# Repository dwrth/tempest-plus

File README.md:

# Tempest-Plus

A remix of the [Tempest](https://github.com/thrly/tempest) keyboard by Oliver Thurley.

Remixed by **dwrth (David Werth)** with:

* An additional number row
* The pinky stretch key moved up by one U

Ergogen configuration included.

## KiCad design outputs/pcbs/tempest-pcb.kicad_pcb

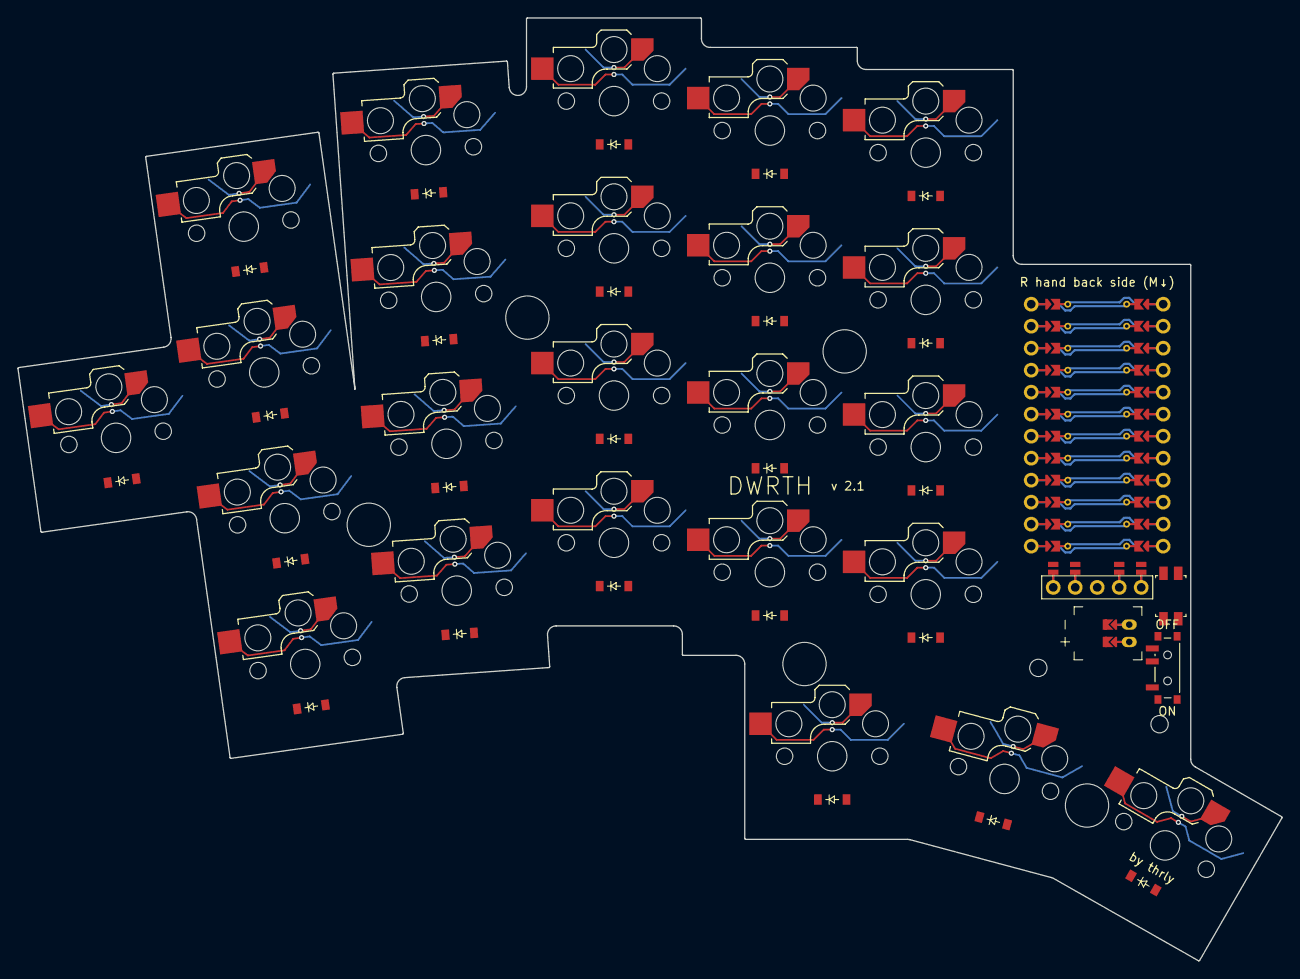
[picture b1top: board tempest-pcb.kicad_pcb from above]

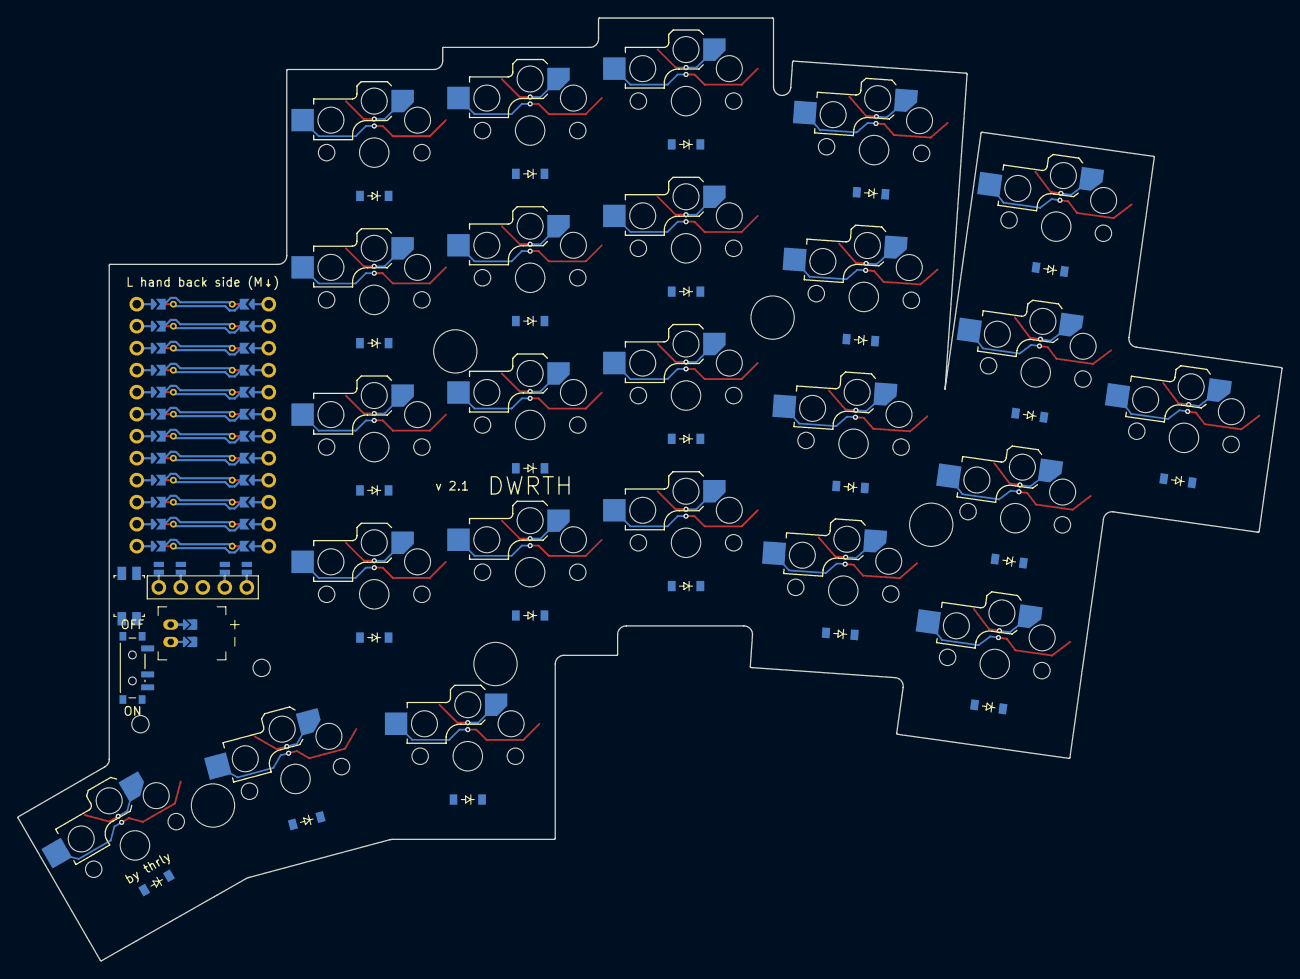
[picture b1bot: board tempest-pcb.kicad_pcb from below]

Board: 2 copper layers, 146.0 x 108.9 mm, 60 parts (24 on the bottom side), 49 nets.

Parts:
D1, D2, D3, D4, D5, D6, D7, D8, D9, D10, D11, D12, D13, D14, D15, D16, D17, D18, D19, D20, D21, D22, D23, D24: diode_tht_sod123
DISP1: display_nice_view
JST1: battery_connector_jst_ph_2
MCU1: mcu_nice_nano
MH1, MH2, MH3, MH4, MH5, MH6, MH7: mounting_hole_npth
PWR1: power_switch_smd_side
RST1: reset_switch_smd_side
S1, S2, S3, S4, S5, S6, S7, S8, S9, S10, S11, S12, S13, S14, S15, S16, S17, S18, S19, S20, S21, S22, S23, S24: switch_choc_v1_v2

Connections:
BAT_P: JST1.1, PWR1.1, PWR1.3
CS: DISP1.14, DISP1.24, MCU1.112
DISP1_1: DISP1.1, DISP1.10, DISP1.23
DISP1_2: DISP1.2, DISP1.11, DISP1.22
DISP1_4: DISP1.4, DISP1.12, DISP1.21
DISP1_5: DISP1.5, DISP1.13, DISP1.20
GND: DISP1.15, DISP1.25, JST1.2, MCU1.102, MCU1.121, MCU1.122, RST1.1, RST1.3
JST1_1: JST1.11, JST1.21, JST1.31
JST1_2: JST1.12, JST1.22, JST1.32
MOSI: DISP1.17, DISP1.27, MCU1.114
RAW: MCU1.101, PWR1.2
RST: MCU1.103, RST1.2, RST1.4
SCK: DISP1.16, DISP1.26, MCU1.113
VCC: DISP1.3, MCU1.104
col_extra: MCU1.105, S1.2
col_index: MCU1.109, S14.2, S15.2, S16.2, S17.2, S23.2
col_inner: MCU1.110, S18.2, S19.2, S20.2, S21.2, S24.2
col_middle: MCU1.108, S10.2, S11.2, S12.2, S13.2, S22.2
col_pinky: MCU1.106, S2.2, S3.2, S4.2, S5.2
col_ring: MCU1.107, S6.2, S7.2, S8.2, S9.2
extra_top: D1.2, S1.1
far_thumb-cluster: D24.2, S24.1
index_bottom: D14.2, S14.1
index_home: D15.2, S15.1
index_num: D17.2, S17.1
index_top: D16.2, S16.1
inner_bottom: D18.2, S18.1
inner_home: D19.2, S19.1
inner_num: D21.2, S21.1
inner_top: D20.2, S20.1
mid_thumb-cluster: D23.2, S23.1
middle_bottom: D10.2, S10.1
middle_home: D11.2, S11.1
middle_num: D13.2, S13.1
middle_top: D12.2, S12.1
near_thumb-cluster: D22.2, S22.1
pinky_bottom: D2.2, S2.1
pinky_home: D3.2, S3.1
pinky_num: D5.2, S5.1
pinky_top: D4.2, S4.1
ring_bottom: D6.2, S6.1
ring_home: D7.2, S7.1
ring_num: D9.2, S9.1
ring_top: D8.2, S8.1
row_bottom: D2.1, D6.1, D10.1, D14.1, D18.1, MCU1.116
row_home: D3.1, D7.1, D11.1, D15.1, D19.1, MCU1.117
row_num: D5.1, D9.1, D13.1, D17.1, D21.1, MCU1.111
row_thumb: D22.1, D23.1, D24.1, MCU1.115
row_top: D1.1, D4.1, D8.1, D12.1, D16.1, D20.1, MCU1.118
